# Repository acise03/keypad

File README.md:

# Keypad

The Keypad is a 4 key macropad.

It is designed to help users easily edit their text documents, by providing features such as space and ctrl + left/right which will help them move past a whole word instead of just one character.

## Features:
- Case
- 2 WS2812B RGB LEDs
- 3 Keys

## CAD Model:
Everything fits together using 4 M3 Bolts and heatset inserts.

It has 2 separate printed pieces. The base where the PCB sits, and the top cover.

## PCB
Here's my PCB! It was made in KiCad.

Schematic

PCB

## Firmware Overview
This hackpad uses [QMK](https://qmk.fm/) firmware for everything. 

- The 3 keys currently act as macros .

## BOM:
Here should be everything you need to make this hackpad

- 3x DSA Keycaps
- 4x M3x5x4 Heatset inserts
- 2x WS2812B LEDs
- 1x XIAO RP2040
- 1x rotary encoder switch
- 1x Case (2 printed parts)

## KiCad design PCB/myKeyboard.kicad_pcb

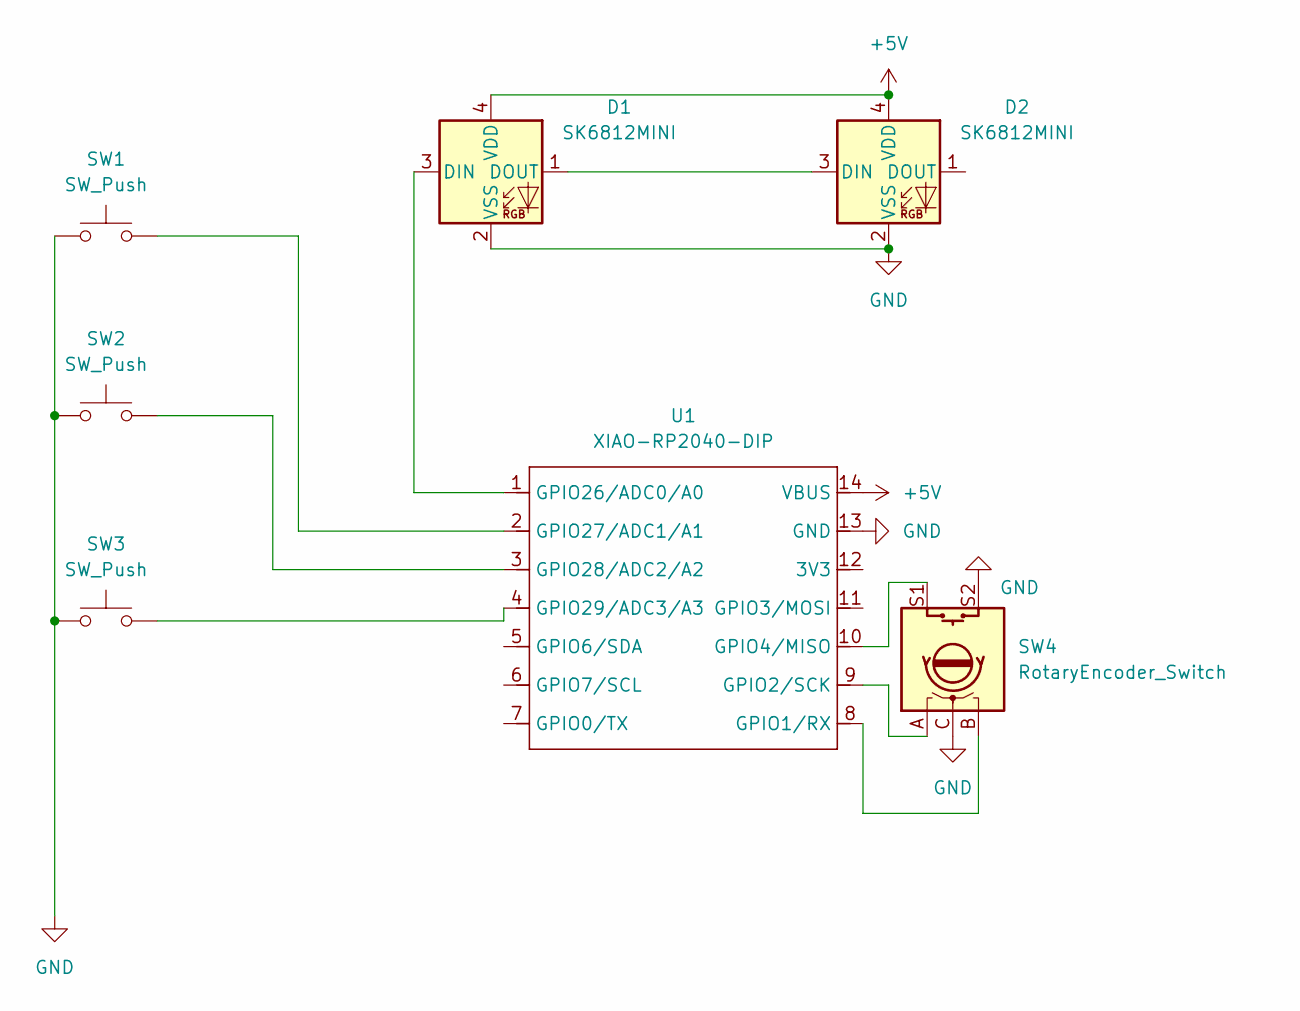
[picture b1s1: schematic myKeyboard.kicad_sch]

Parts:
D1, D2: SK6812MINI; LED_SK6812MINI_PLCC4_3.5x3.5mm_P1.75mm
SW1, SW2, SW3: SW_Push; SW_Cherry_MX_1.00u_PCB
SW4: RotaryEncoder_Switch; RotaryEncoder_Alps_EC11E-Switch_Vertical_H20mm_MountingHoles
U1: XIAO-RP2040-DIP

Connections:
+5V: D1.4 (VDD), D2.4 (VDD), U1.14 (VBUS)
GND: D1.2 (VSS), D2.2 (VSS), SW1.1, SW2.1, SW3.1, SW4.C, SW4.S2, U1.13 (GND)
unnamed: D1.3 (DIN), U1.1 (GPIO26/ADC0/A0)
unnamed: D1.1 (DOUT), D2.3 (DIN)
unnamed: SW4.B, U1.8 (GPIO1/RX)
unnamed: SW4.A, U1.9 (GPIO2/SCK)
unnamed: SW4.S1, U1.10 (GPIO4/MISO)
unnamed: SW1.2, U1.2 (GPIO27/ADC1/A1)
unnamed: SW2.2, U1.3 (GPIO28/ADC2/A2)
unnamed: SW3.2, U1.4 (GPIO29/ADC3/A3)

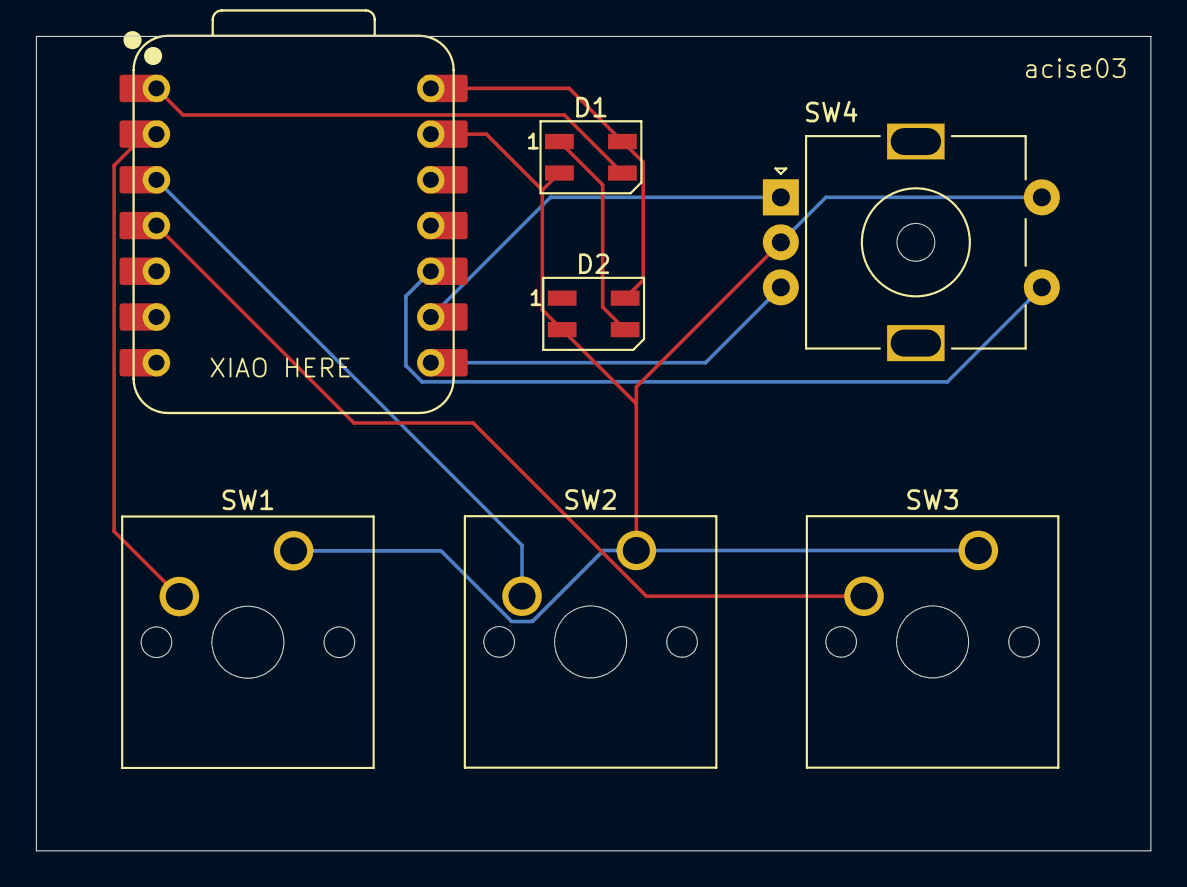
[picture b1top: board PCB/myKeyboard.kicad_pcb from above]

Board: 2 copper layers, 61.9 x 45.2 mm, 7 parts (0 on the bottom side), 10 nets.

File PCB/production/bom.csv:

Designator,Footprint,Quantity,Value,LCSC Part #
"D1, D2",LED_SK6812MINI_PLCC4_3.5x3.5mm_P1.75mm,2,SK6812MINI,
"SW1, SW2, SW3",SW_Cherry_MX_1.00u_PCB,3,SW_Push,
SW4,RotaryEncoder_Alps_EC11E-Switch_Vertical_H20mm_MountingHoles,1,RotaryEncoder_Switch,
U1,XIAO-RP2040-DIP,1,XIAO-RP2040-DIP,

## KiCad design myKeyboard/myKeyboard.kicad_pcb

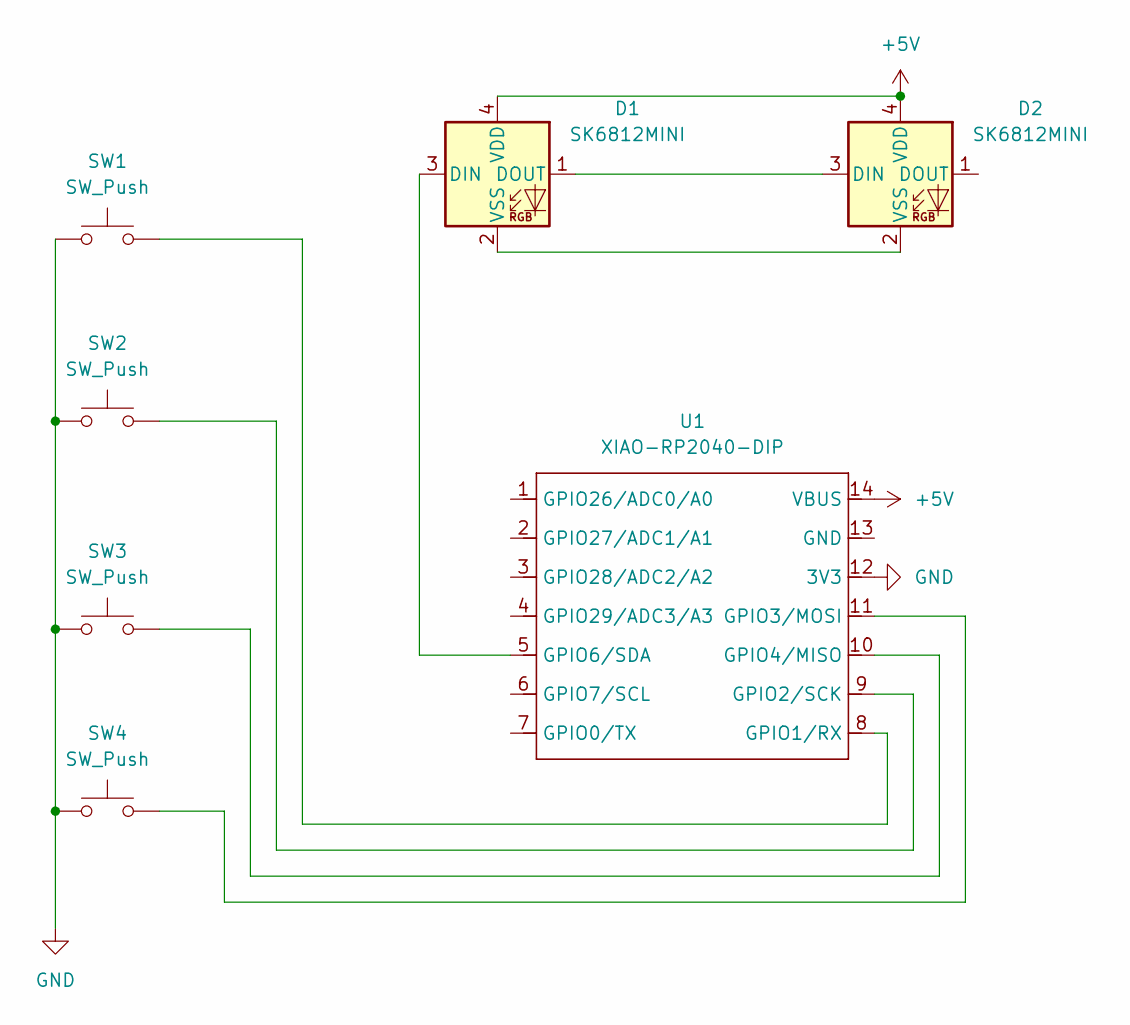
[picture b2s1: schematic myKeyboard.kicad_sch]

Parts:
D1, D2: SK6812MINI; LED_SK6812MINI_PLCC4_3.5x3.5mm_P1.75mm
SW1, SW2, SW3, SW4: SW_Push; SW_Cherry_MX_1.00u_PCB
U1: XIAO-RP2040-DIP

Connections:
+5V: D1.4 (VDD), D2.4 (VDD), U1.14 (VBUS)
GND: SW1.1, SW2.1, SW3.1, SW4.1, U1.12 (3V3)
unnamed: D1.3 (DIN), U1.5 (GPIO6/SDA)
unnamed: D1.1 (DOUT), D2.3 (DIN)
unnamed: D1.2 (VSS), D2.2 (VSS)
unnamed: SW1.2, U1.8 (GPIO1/RX)
unnamed: SW2.2, U1.9 (GPIO2/SCK)
unnamed: SW4.2, U1.11 (GPIO3/MOSI)
unnamed: SW3.2, U1.10 (GPIO4/MISO)

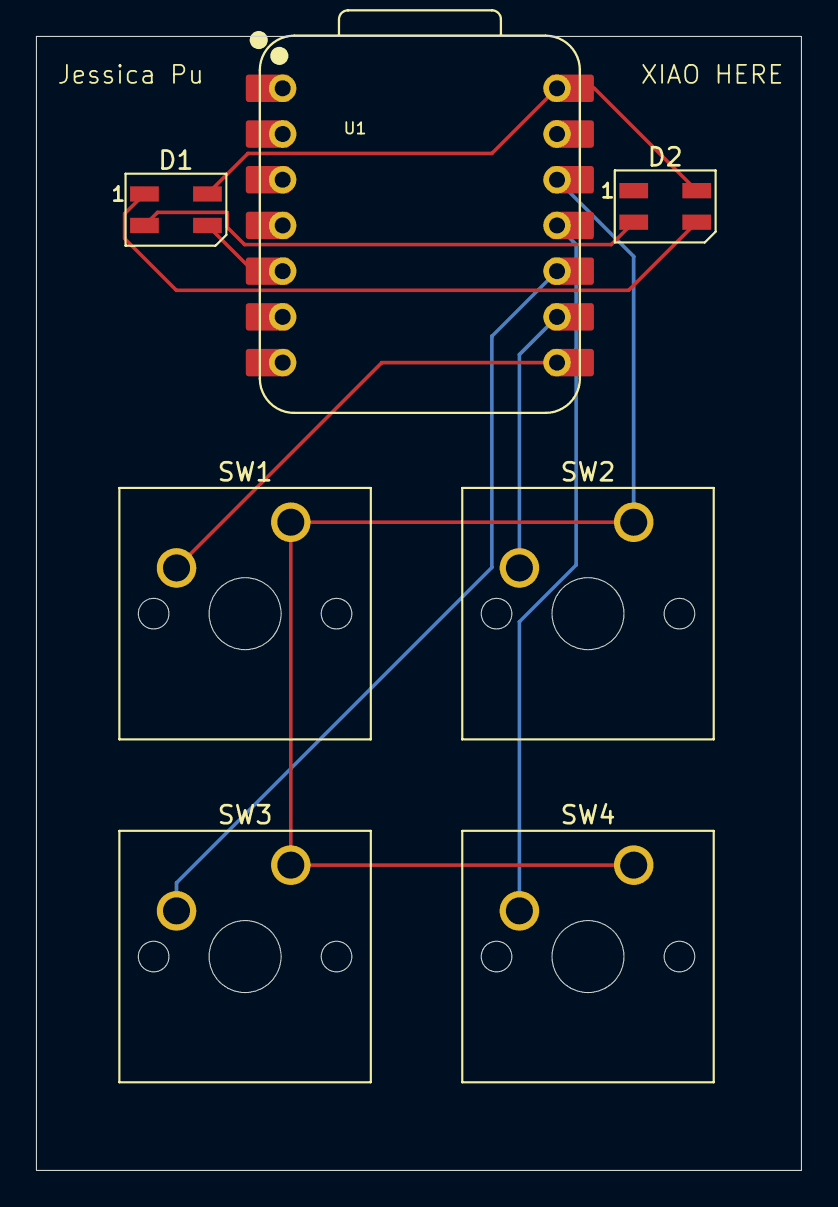
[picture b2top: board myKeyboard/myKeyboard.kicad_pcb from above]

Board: 2 copper layers, 42.5 x 63.0 mm, 7 parts (0 on the bottom side), 9 nets.

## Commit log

2025-06-15 organize files
